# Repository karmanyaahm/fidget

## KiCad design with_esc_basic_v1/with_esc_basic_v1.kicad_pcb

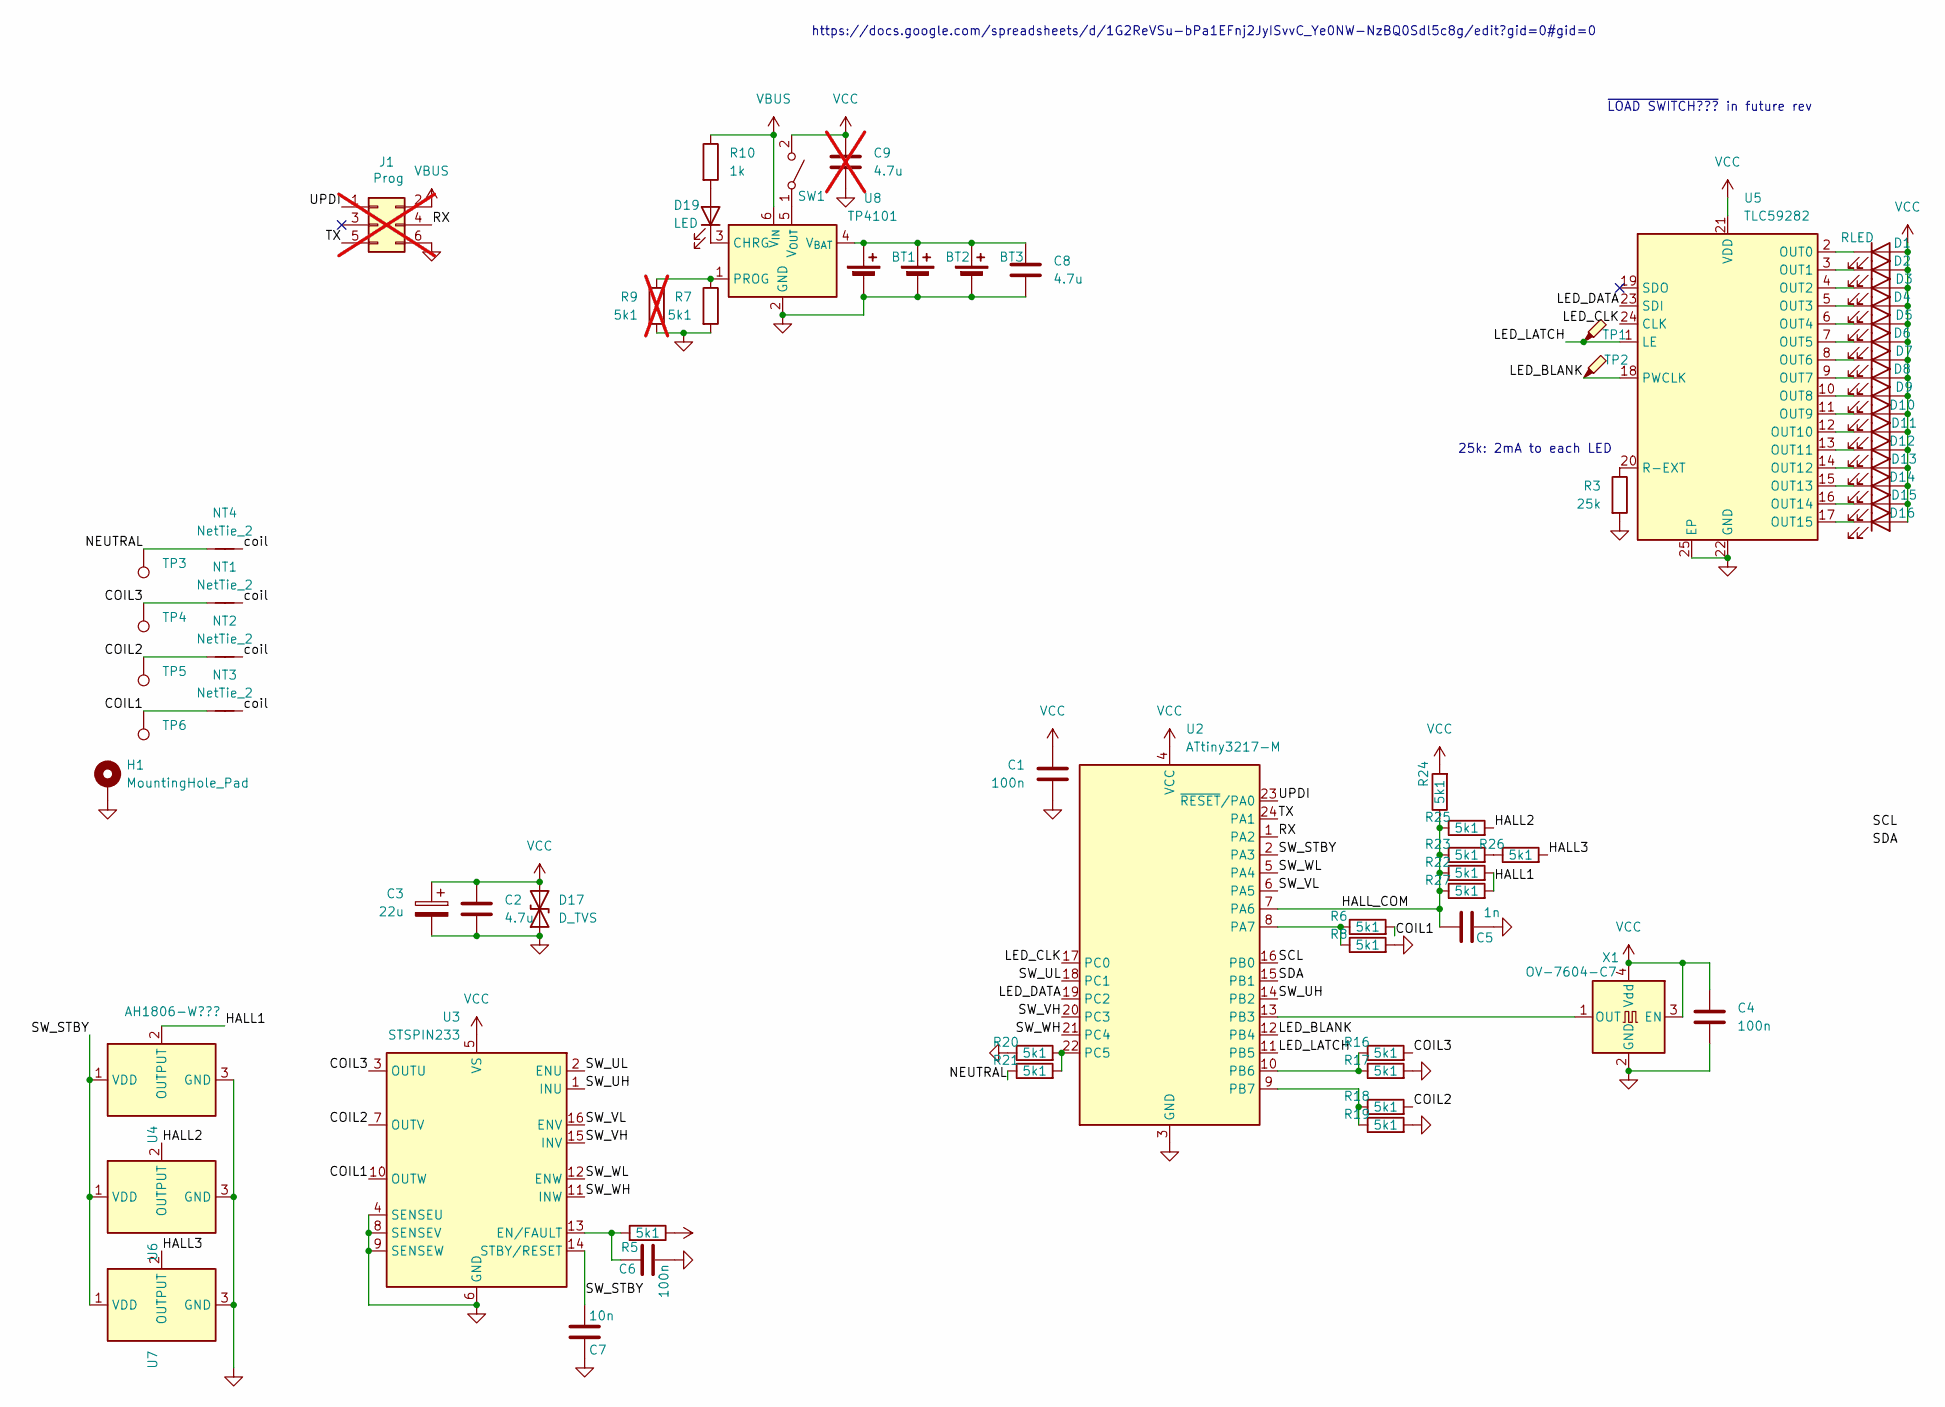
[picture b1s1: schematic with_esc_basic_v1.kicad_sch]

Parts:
BT1, BT2, BT3: Battery_Cell; BAT_BK-5009
C1, C4, C6: 100n; C_0402_1005Metric
C2, C8: 4.7u; C_0603_1608Metric
C3: 22u; CP_Elec_4x5.4
C5: 1n; C_0402_1005Metric
C7: 10n; C_0402_1005Metric
C9: 4.7u; C_0603_1608Metric; not fitted
D1, D2, D3, D4, D5, D6, D7, D8, D9, D10, D11, D12, D13, D14, D15, D16: RLED; LED_0402_1005Metric
D17: D_TVS; D_0603_1608Metric
D19: LED; LED_0402_1005Metric
H1: MountingHole_Pad; MountingHole_2.2mm_M2_Pad_thin
J1: Prog; IDC-Header_2x03_P2.54mm_Vertical; not fitted
NT1, NT2, NT3, NT4: NetTie_2; NetTie-2_SMD_Pad0.5mm
R3: 25k; R_0402_1005Metric
R5, R6, R7, R8, R16, R17, R18, R19, R20, R21, R22, R23, R24, R25, R26, R27: 5k1; R_0402_1005Metric
R9: 5k1; R_0402_1005Metric; not fitted
R10: 1k; R_0402_1005Metric
SW1: SW_SPST; SW_SPDT_PCM12; LCSC C963206
TP1, TP2: TestPoint_Probe; TestPoint_THTPad_1.0x1.0mm_Drill0.5mm
TP3, TP4, TP5, TP6: TestPoint; TestPoint_THTPad_1.5x1.5mm_Drill0.7mm
U2: ATtiny3217-M; QFN-24-1EP_4x4mm_P0.5mm_EP2.6x2.6mm
U3: STSPIN233; VQFN-16-1EP_3x3mm_P0.5mm_EP1.8x1.8mm
U4, U6, U7: AH1806-W???; SC-59
U5: TLC59282; QFN-24-1EP_4x4mm_P0.5mm_EP2.15x2.15mm
U8: TP4101; SOT-23-6
X1: OV-7604-C7; OSC_OV-7604-C7-32.768KHZ-20PPM-TB-QA

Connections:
/COIL1: NT3.1, R6.2, TP6.1, U3.10 (OUTW)
/COIL2: NT2.1, R18.2, TP5.1, U3.7 (OUTV)
/COIL3: NT1.1, R16.2, TP4.1, U3.3 (OUTU)
/HALL1: R22.2, R27.2, U4.2 (OUTPUT)
/HALL2: R25.2, U6.2 (OUTPUT)
/HALL3: R26.2, U7.2 (OUTPUT)
/HALL_COM: C5.1, R22.1, R23.1, R24.1, R25.1, R27.1, U2.7 (PA6)
/LED_BLANK: TP2.1, U2.12 (PB4), U5.18 (PWCLK)
/LED_CLK: U2.17 (PC0), U5.24 (CLK)
/LED_DATA: U2.19 (PC2), U5.23 (SDI)
/LED_LATCH: TP1.1, U2.11 (PB5), U5.1 (LE)
/NEUTRAL: NT4.1, R21.1, TP3.1
/RX: J1.4, U2.1 (PA2)
/SCL: U2.16 (PB0)
/SDA: U2.15 (PB1)
/SW_STBY: C7.2, U2.2 (PA3), U3.14 (STBY/RESET), U4.1 (VDD), U6.1 (VDD), U7.1 (VDD)
/SW_UH: U2.14 (PB2), U3.1 (INU)
/SW_UL: U2.18 (PC1), U3.2 (ENU)
/SW_VH: U2.20 (PC3), U3.15 (INV)
/SW_VL: U2.6 (PA5), U3.16 (ENV)
/SW_WH: U2.21 (PC4), U3.11 (INW)
/SW_WL: U2.5 (PA4), U3.12 (ENW)
/TX: J1.5, U2.24 (PA1)
/UPDI: J1.1, U2.23 (~RESET/PA0)
/coil: NT1.2, NT2.2, NT3.2, NT4.2
GND: BT1.2 (-), BT2.2 (-), BT3.2 (-), C1.2, C2.2, C3.2, C4.2, C5.2, C6.2, C7.1, C8.2, C9.2, D17.1 (A1), H1.1, J1.6, R3.2, R7.2, R8.2, R9.2, R17.2, R19.2, R20.1, U2.3 (GND), U2.25 (GND), U3.4 (SENSEU), U3.6 (GND), U3.8 (SENSEV), U3.9 (SENSEW), U3.17 (GND), U4.3 (GND), U5.22 (GND), U5.25 (EP), U6.3 (GND), U7.3 (GND), U8.2 (GND), X1.2 (GND)
unnamed: BT1.1 (+), BT2.1 (+), BT3.1 (+), C8.1, U8.4 (V_{BAT})
unnamed: D1.1 (K), U5.2 (OUT0)
unnamed: D2.1 (K), U5.3 (OUT1)
unnamed: D3.1 (K), U5.4 (OUT2)
unnamed: D4.1 (K), U5.5 (OUT3)
unnamed: D5.1 (K), U5.6 (OUT4)
unnamed: D6.1 (K), U5.7 (OUT5)
unnamed: D7.1 (K), U5.8 (OUT6)
unnamed: D8.1 (K), U5.9 (OUT7)
unnamed: D9.1 (K), U5.10 (OUT8)
unnamed: D10.1 (K), U5.11 (OUT9)
unnamed: D11.1 (K), U5.12 (OUT10)
unnamed: D12.1 (K), U5.13 (OUT11)
unnamed: D13.1 (K), U5.14 (OUT12)
unnamed: D14.1 (K), U5.15 (OUT13)
unnamed: D15.1 (K), U5.16 (OUT14)
unnamed: D16.1 (K), U5.17 (OUT15)
unnamed: D19.2 (A), R10.2
unnamed: D19.1 (K), U8.3 (CHRG)
unnamed: R23.2, R26.1
unnamed: SW1.1 (A), U8.5 (V_{OUT})
unnamed: R6.1, R8.1, U2.8 (PA7)
unnamed: U2.13 (PB3), X1.1 (OUT)
unnamed: R16.1, R17.1, U2.10 (PB6)
unnamed: R18.1, R19.1, U2.9 (PB7)
unnamed: R20.2, R21.2, U2.22 (PC5)
unnamed: C6.1, R5.2, U3.13 (EN/FAULT)
unnamed: R3.1, U5.20 (R-EXT)
unnamed: R7.1, R9.1, U8.1 (PROG)
VBUS: J1.2, R10.1, U8.6 (V_{IN})
VCC: C1.1, C2.1, C3.1, C4.1, C9.1, D1.2 (A), D2.2 (A), D3.2 (A), D4.2 (A), D5.2 (A), D6.2 (A), D7.2 (A), D8.2 (A), D9.2 (A), D10.2 (A), D11.2 (A), D12.2 (A), D13.2 (A), D14.2 (A), D15.2 (A), D16.2 (A), D17.2 (A2), R5.1, R24.2, SW1.2 (B), U2.4 (VCC), U3.5 (VS), U5.21 (VDD), X1.3 (EN), X1.4 (Vdd)

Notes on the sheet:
~{LOAD SWITCH???} in future rev
25k: 2mA to each LED
https://docs.google.com/spreadsheets/d/1G2ReVSu-bPa1EFnj2JyISvvC_Ye0NW-NzBQ0Sdl5c8g/edit?gid=0#gid=0

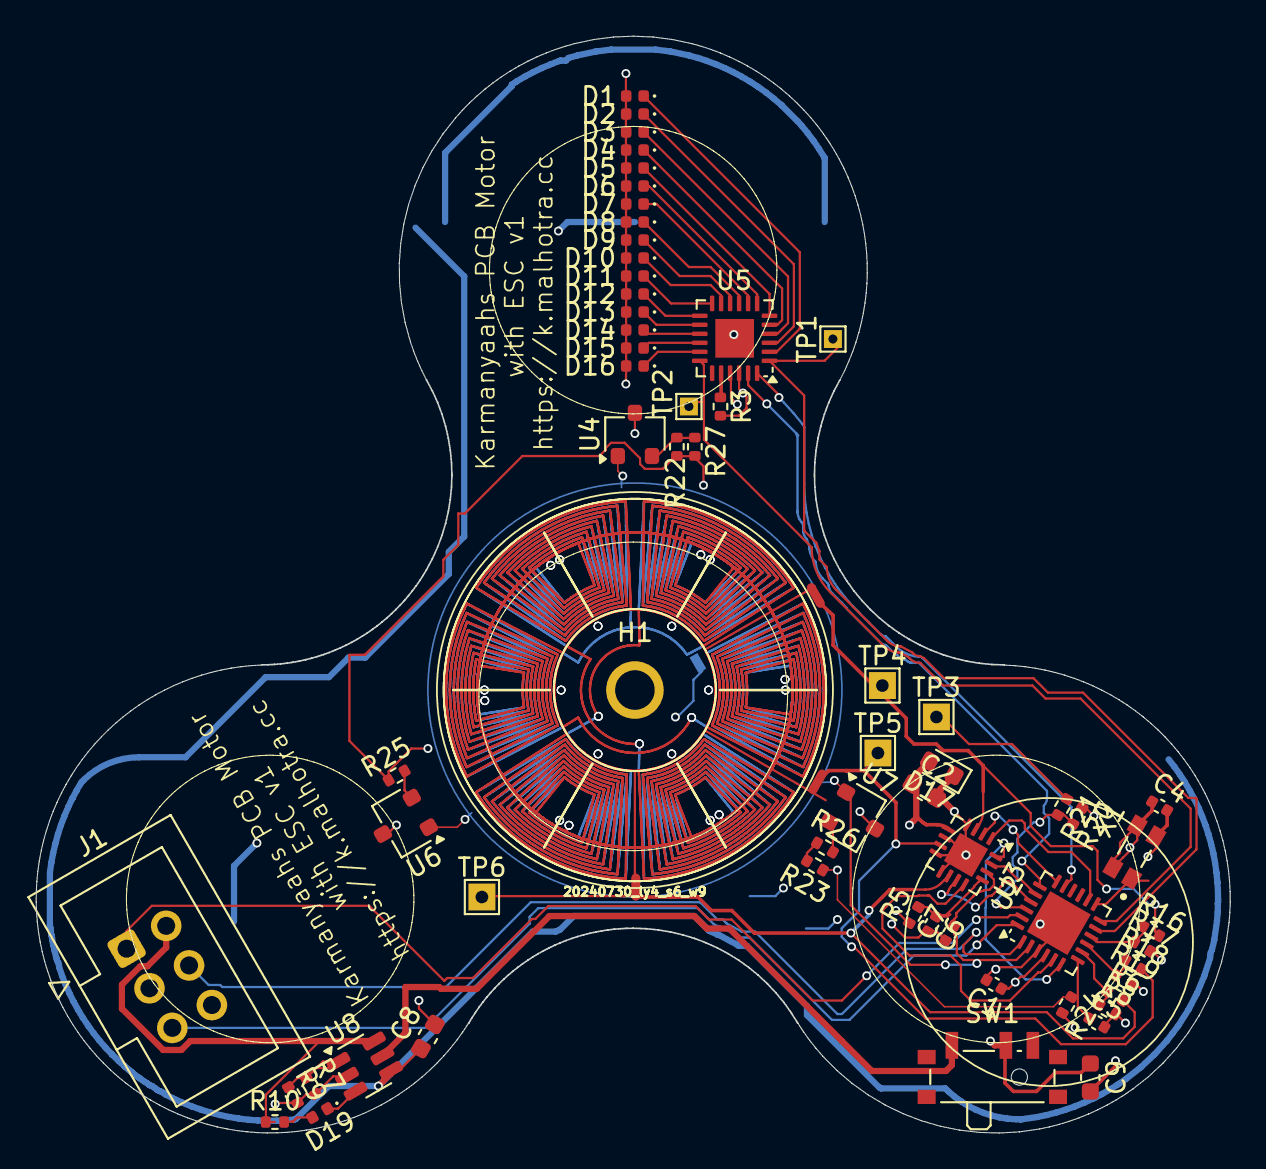
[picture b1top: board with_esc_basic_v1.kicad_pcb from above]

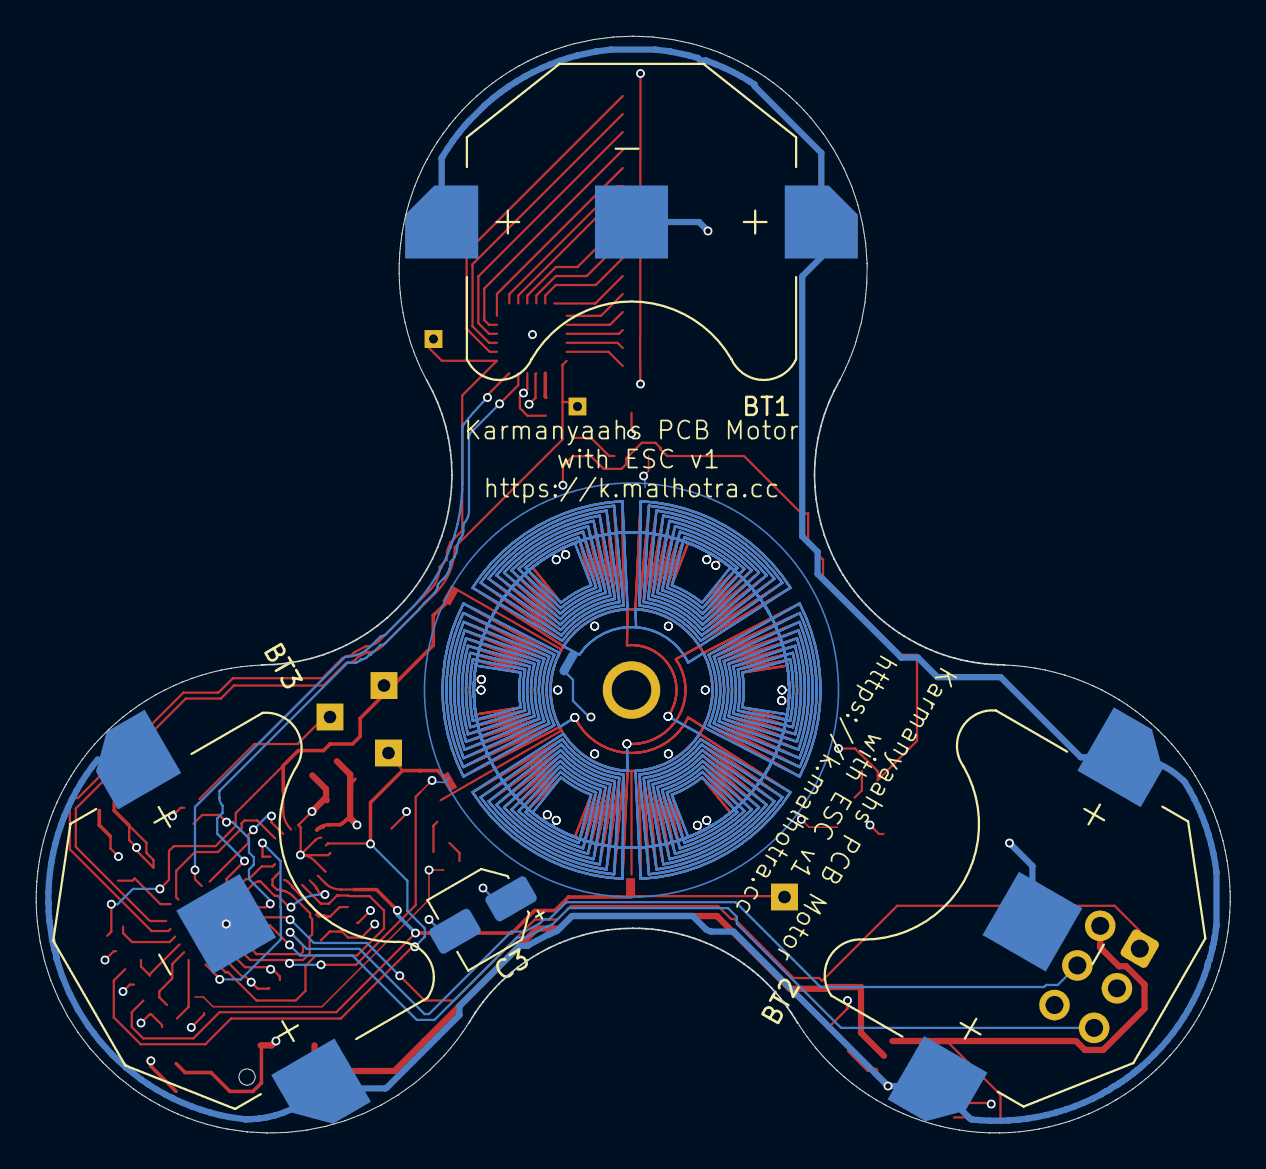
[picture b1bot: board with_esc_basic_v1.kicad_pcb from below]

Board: 4 copper layers, 66.3 x 60.9 mm, 70 parts (5 on the bottom side), 55 nets.

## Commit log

2024-07-20 init
2024-07-20 notes
2024-08-05 a lot of updates; working v1
